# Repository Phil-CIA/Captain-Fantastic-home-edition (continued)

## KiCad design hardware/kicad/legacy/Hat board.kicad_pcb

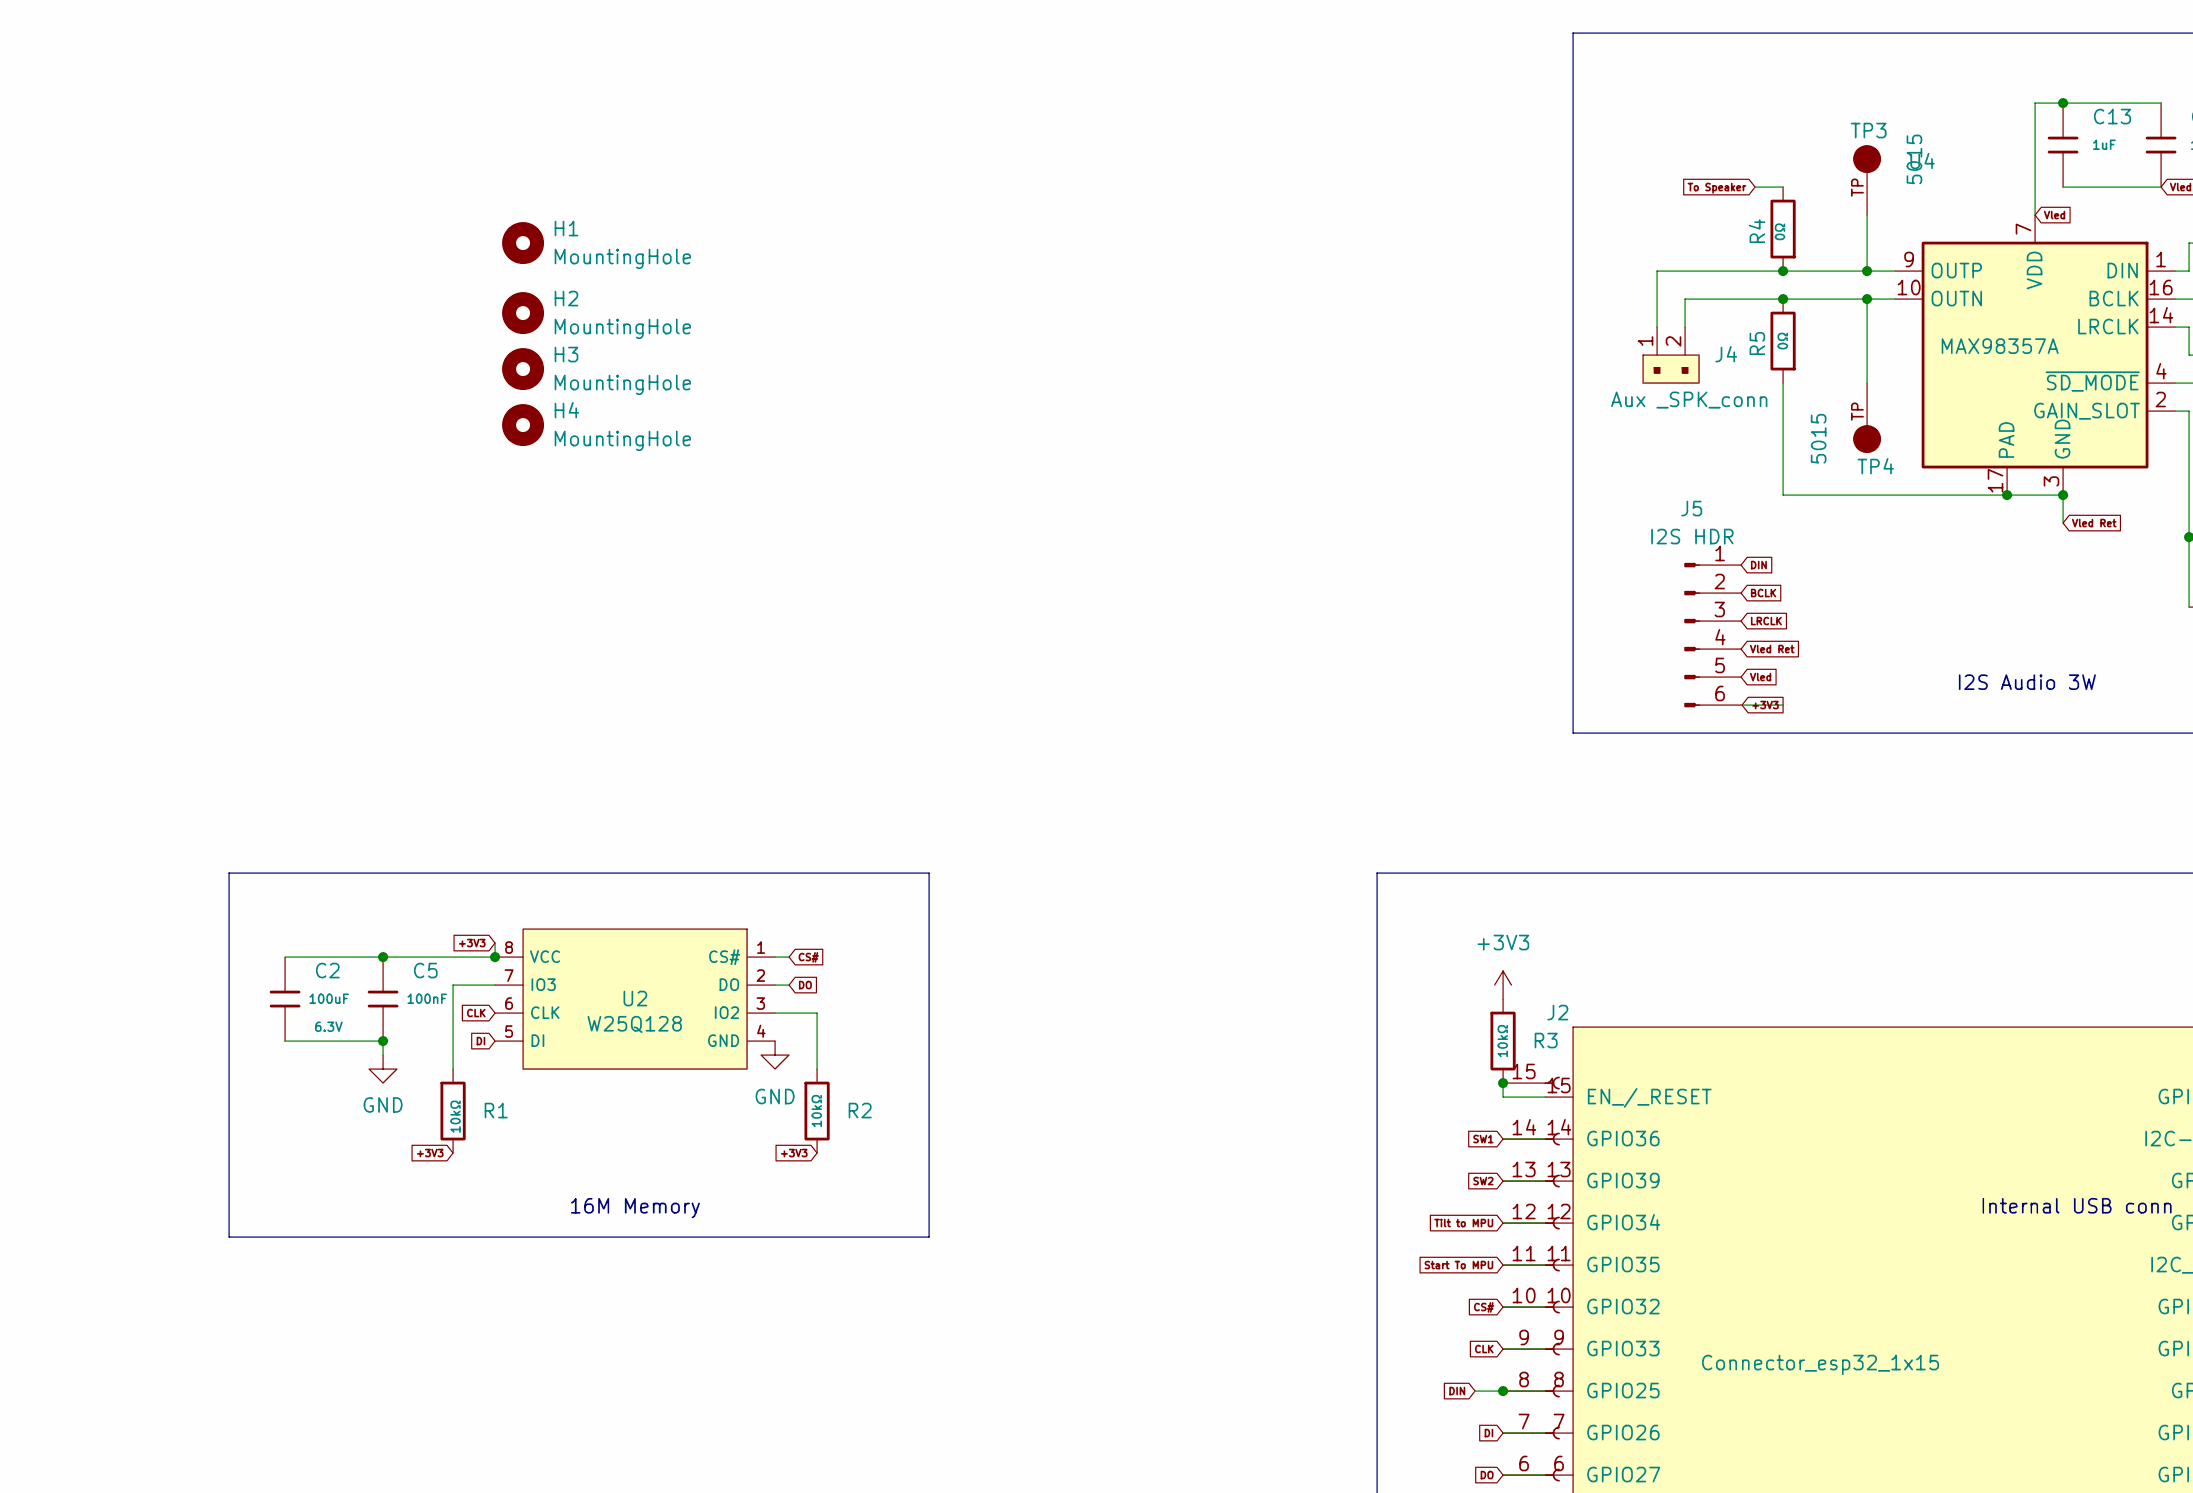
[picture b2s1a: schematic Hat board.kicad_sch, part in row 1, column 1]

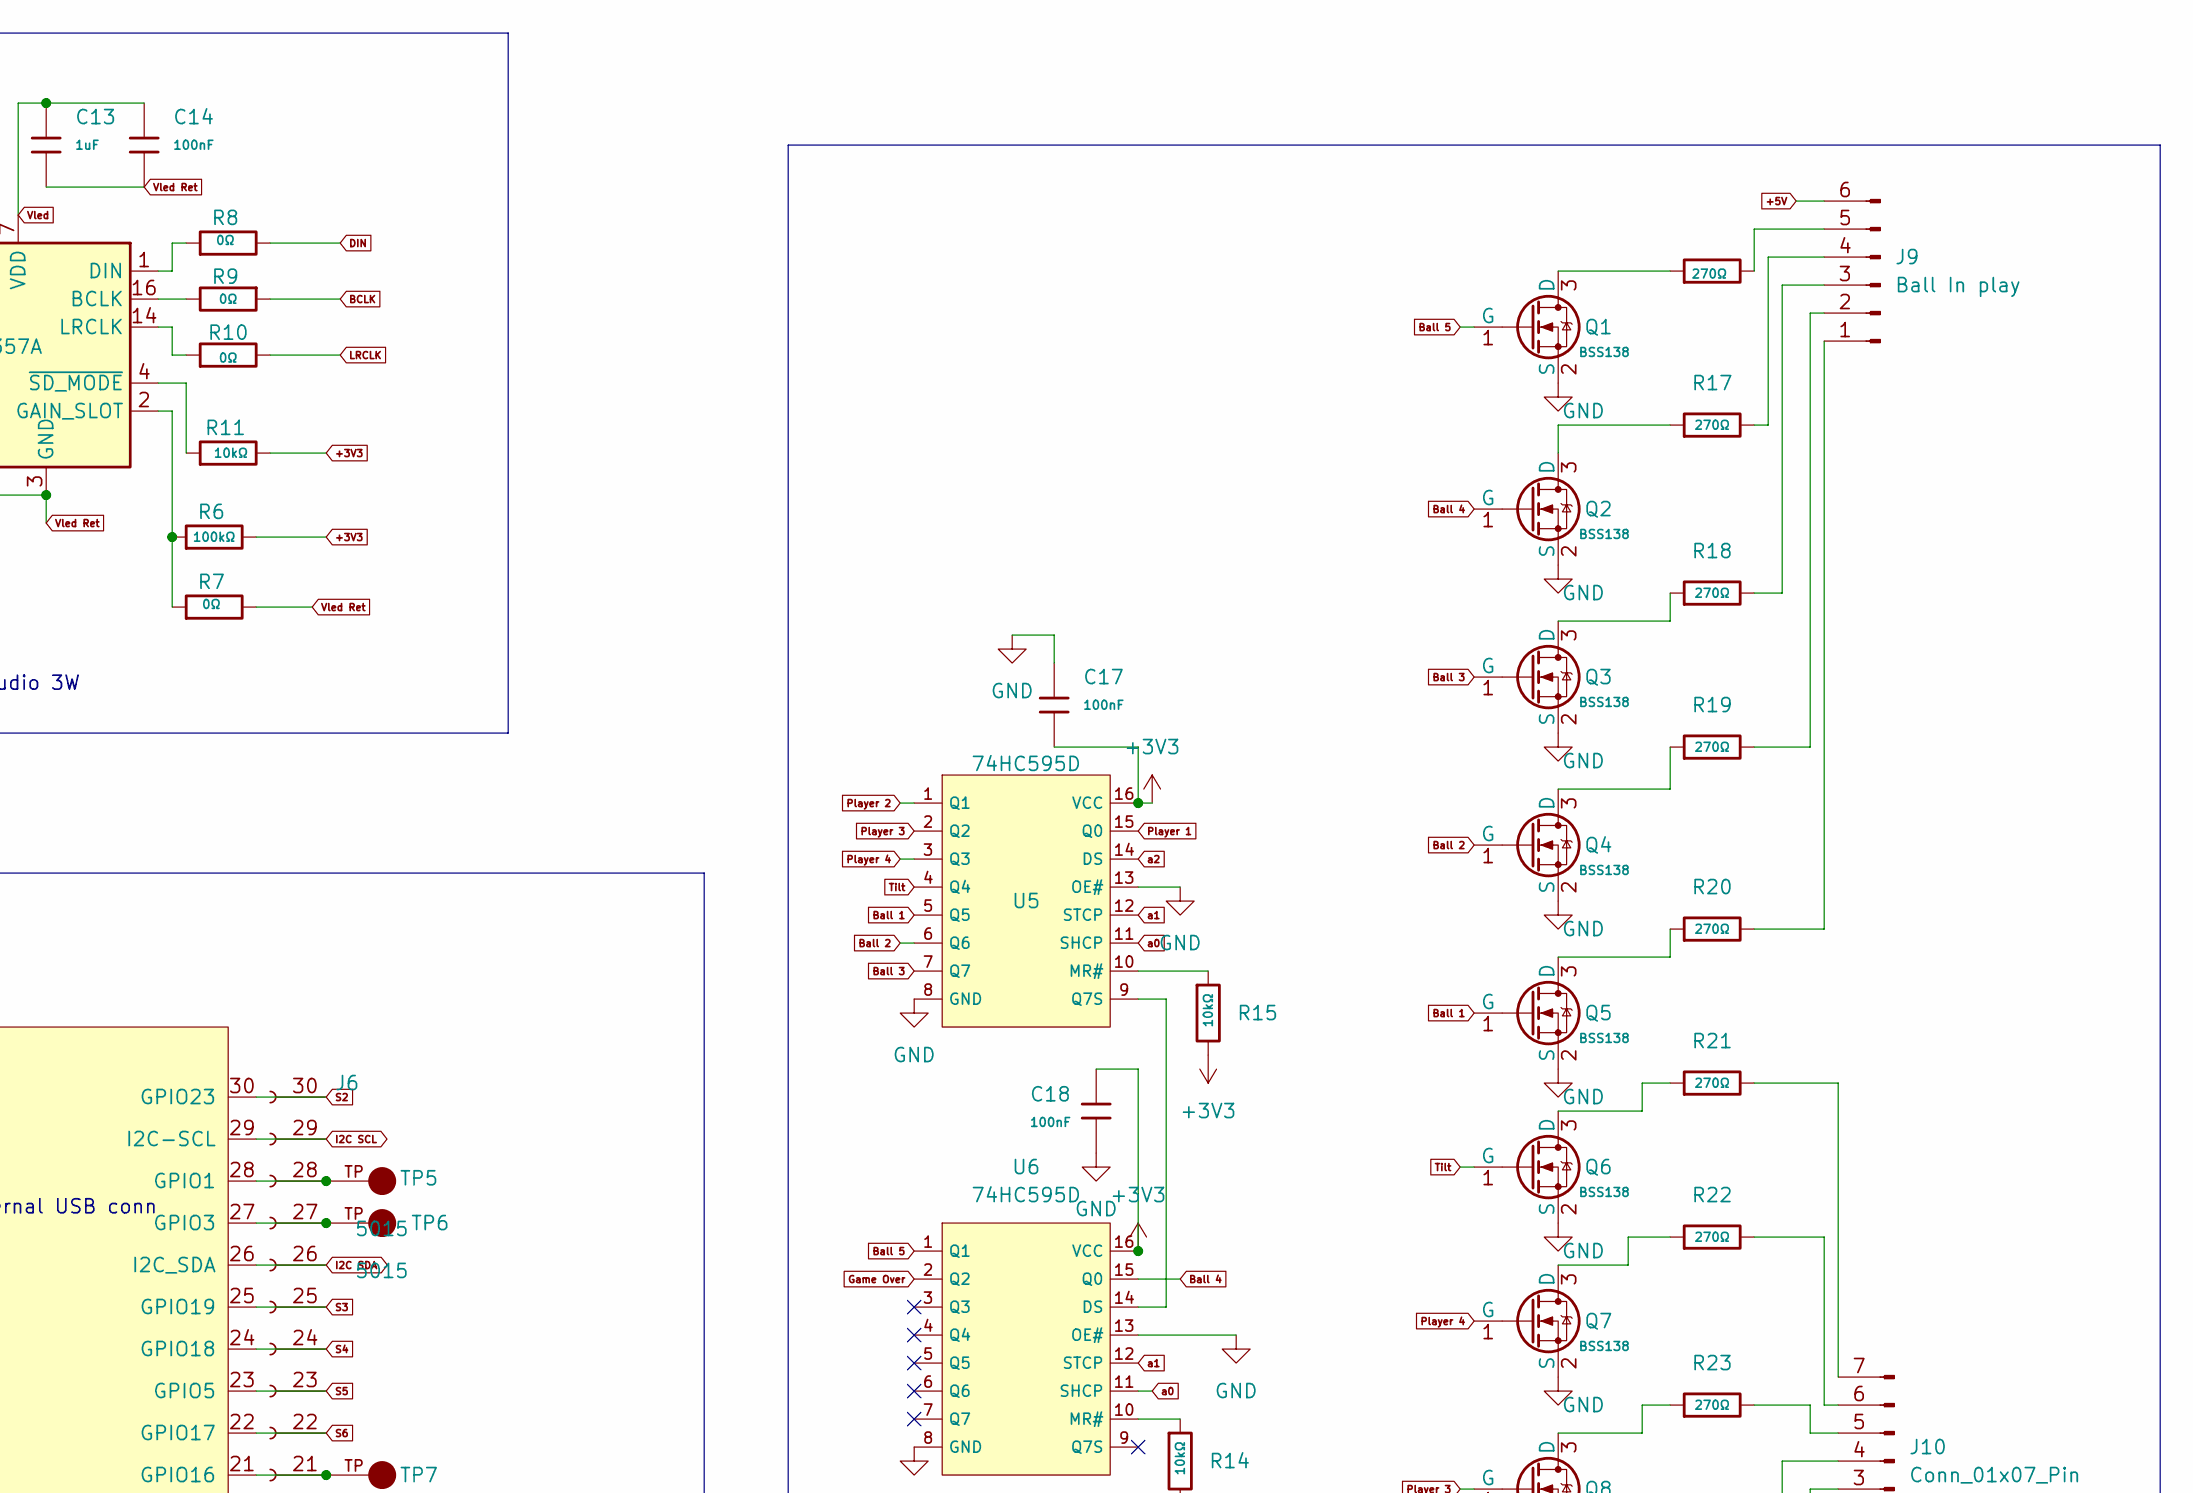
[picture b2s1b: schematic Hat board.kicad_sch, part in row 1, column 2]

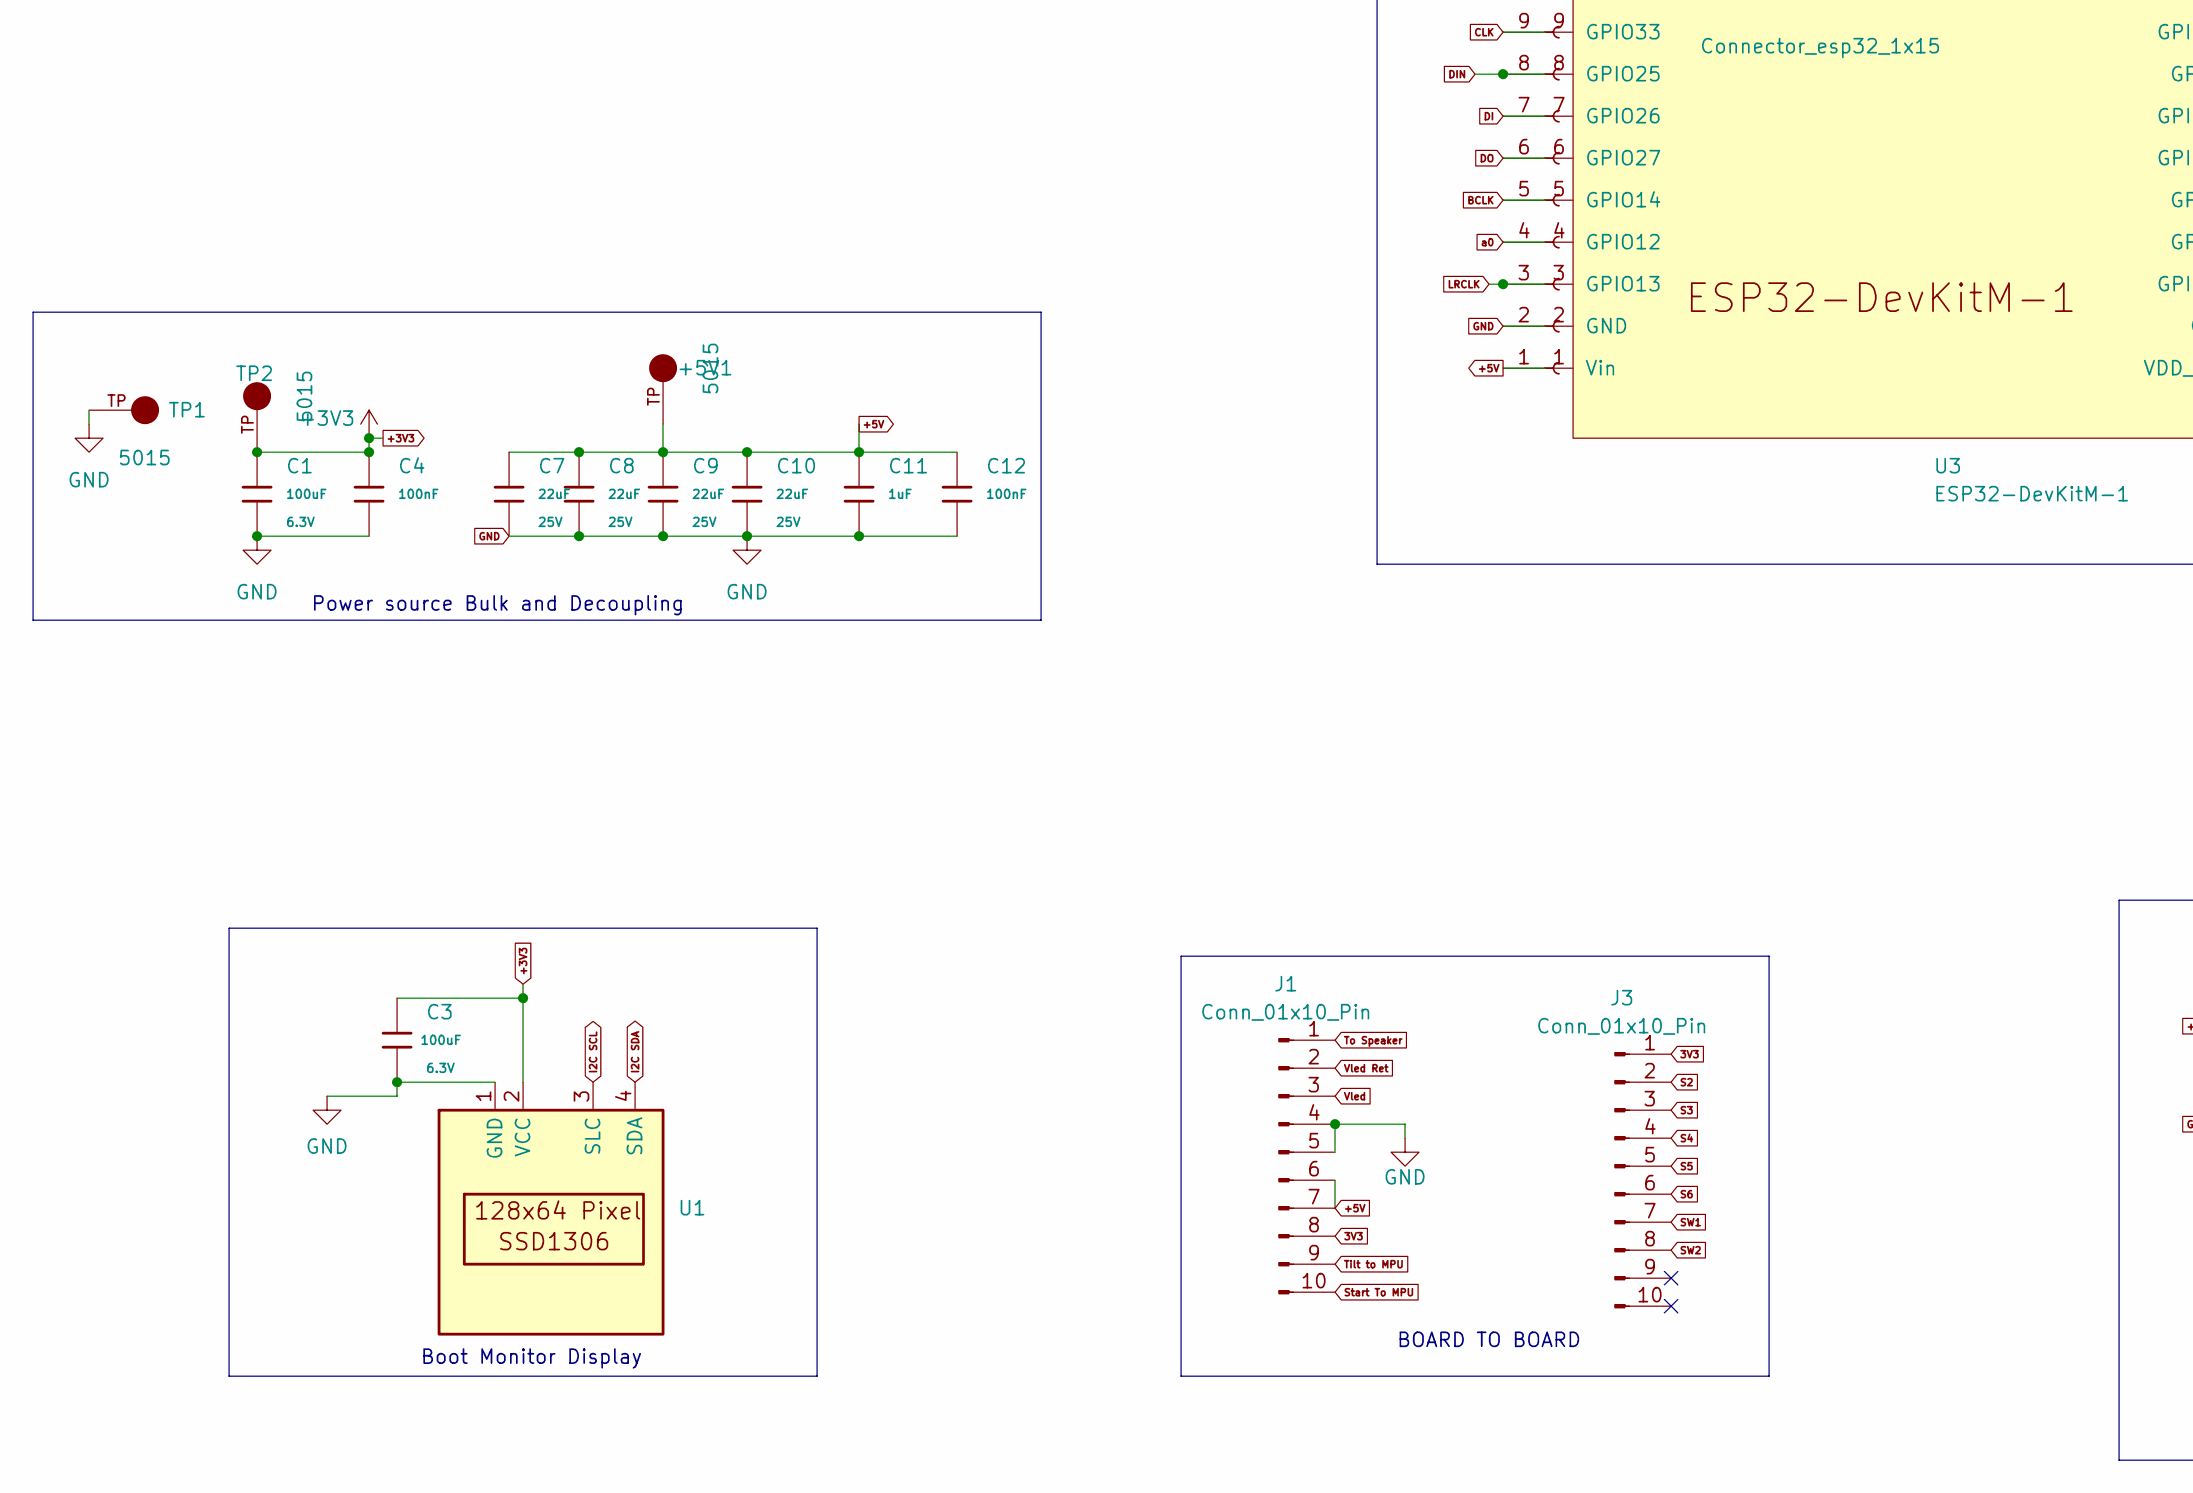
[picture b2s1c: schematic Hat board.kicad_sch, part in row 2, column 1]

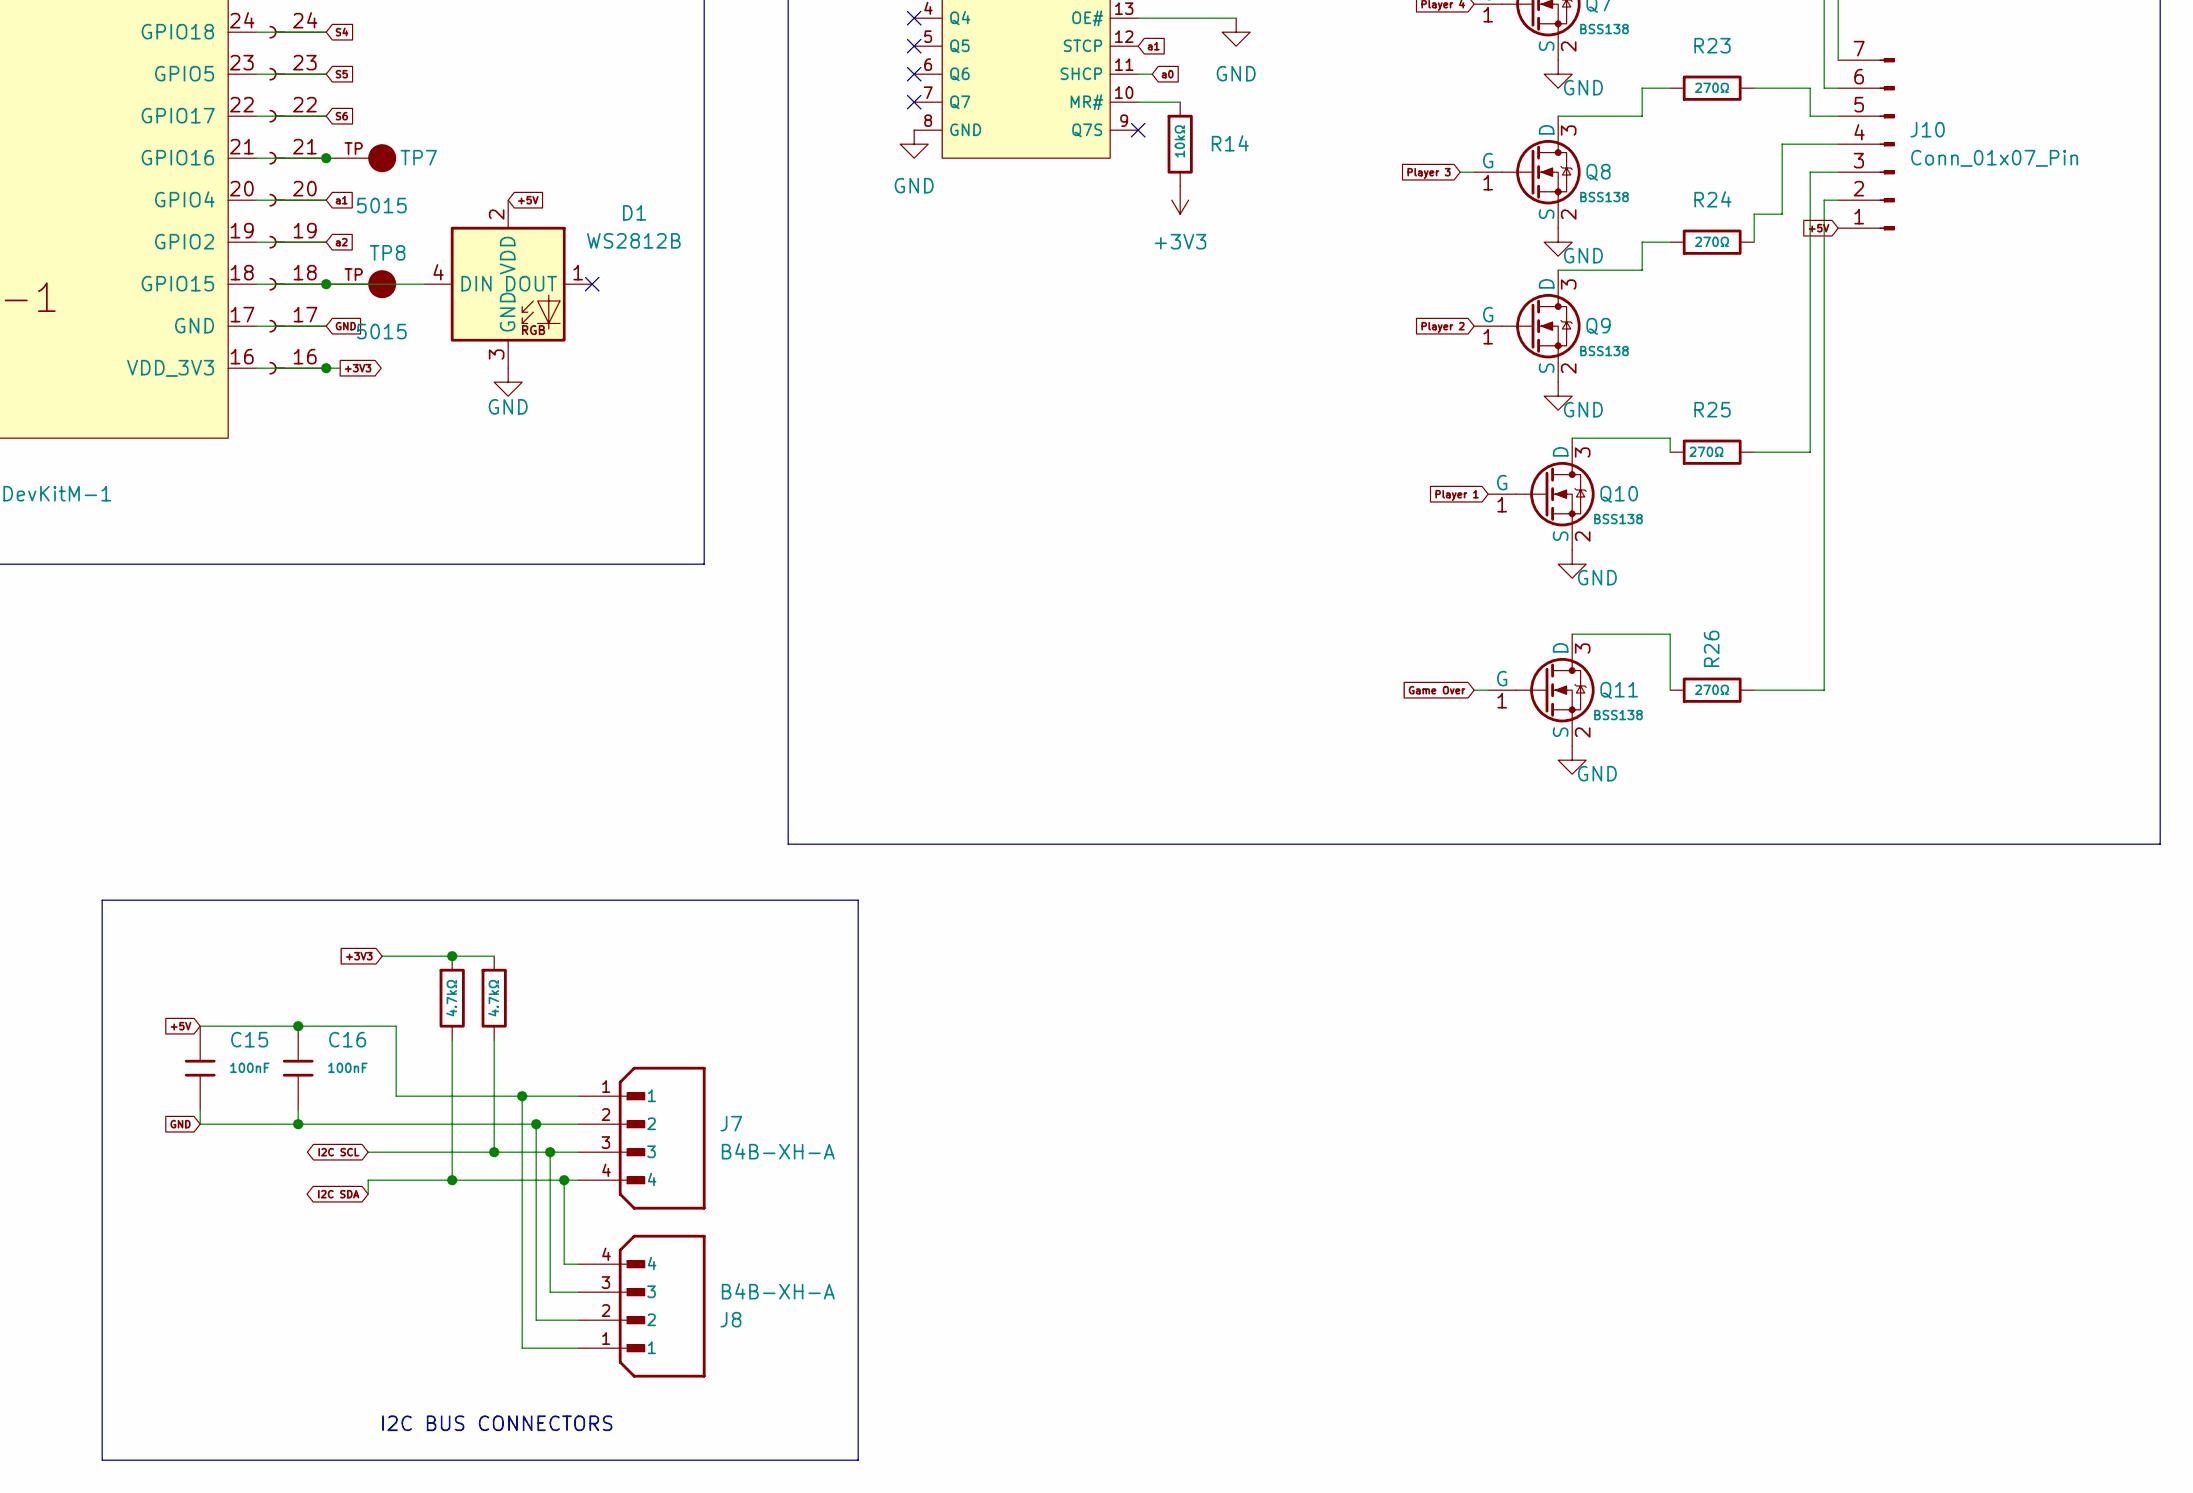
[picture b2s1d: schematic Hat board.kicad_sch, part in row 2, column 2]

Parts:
+5V1: 5015; KEYSTONE_5015; MPN 5015; Digi-Key_PN 36-5015CT-ND
C1, C2, C3: 100uF; C_1206; Voltage Rated 6.3V; Tolerance ±20%; Part CL31A107MQHNNNE; LCSC C15008
C4, C5, C12, C14, C15, C16, C17, C18: 100nF; C_0805; Voltage Rated 50V; Tolerance ±10%; Part CC0805KRX7R9BB104; LCSC C49678
C7, C8, C9, C10: 22uF; C_0805; Voltage Rated 25V; Tolerance ±20%; Part CL21A226MAQNNNE; LCSC C45783
C11, C13: 1uF; C_0805; Voltage Rated 50V; Tolerance ±10%; Part CL21B105KBFNNNE; LCSC C28323
D1: WS2812B; LED-SMD_4P-L1.6-W1.5_XL-1615RGBC-WS2812B; LCSC C5349954
H1, H2, H3, H4: MountingHole; MountingHole_3.5mm_Pad
J1, J3: Conn_01x10_Pin; PinHeader_1x10_P2.54mm_Vertical
J2, J6: Connector_esp32_1x15; PinSocket_1x15_P2.54mm_Vertical
J4: Aux _SPK_conn; JST_XH_B2B-XH-A_1x02_P2.50mm_Vertical; MPN B2B-XH-A(LF)(SN); Digi-Key_PN 455-2247-ND
J5: I2S HDR; PinHeader_1x06_P2.54mm_Vertical_SMD_Pin1Right
J7, J8: B4B-XH-A; JST_EH_B4B-EH-A_1x04_P2.50mm_Vertical; PARTREV 7/4/21
J9: Ball In play; JST_XH_B6B-XH-AM_1x06_P2.50mm_Vertical
J10: Conn_01x07_Pin; JST_XH_B7B-XH-AM_1x07_P2.50mm_Vertical
Q1, Q2, Q3, Q4, Q5, Q6, Q7, Q8, Q9, Q10, Q11: BSS138; Q_SOT-23; Part BSS138; LCSC C7420339
R1, R2, R3, R11, R14, R15: 10kΩ; R_0805; Overload Voltage (Max) 150V; Tolerance ±1%; Part 0805W8F1002T5E; LCSC C17414
R4, R5, R7, R8, R9, R10: 0Ω; R_0805; Overload Voltage (Max) 150V; Tolerance ±1%; Part 0805W8F0000T5E; LCSC C17477
R6: 100kΩ; R_0805; Overload Voltage (Max) 150V; Tolerance ±1%; Part 0805W8F1003T5E; LCSC C149504
R12, R13: 4.7kΩ; R_0805; Overload Voltage (Max) 150V; Tolerance ±1%; Part 0805W8F4701T5E; LCSC C17673
R16, R17, R18, R19, R20, R21, R22, R23, R24, R25, R26: 270Ω; R_0805; Overload Voltage (Max) 150V; Tolerance ±1%; Part 0805W8F2700T5E; LCSC C17590
TP1, TP2, TP3, TP4, TP6, TP7, TP8: 5015; KEYSTONE_5015; MPN 5015; Digi-Key_PN 36-5015CT-ND
TP5: 5015; KEYSTONE_5015; Part 5015; LCSC C5199798
U1: ).96 inOLED display SSD1306
U2: W25Q128; SOIC-8_L5.3-W5.3-P1.27-LS8.0-BL; Part W25Q128JVSIQ; LCSC C97521
U3: ESP32-DevKitM-1
U4: MAX98357A; TQFN-16-1EP_3x3mm_P0.5mm_EP1.23x1.23mm
U5, U6: 74HC595D; SOIC-16_L9.9-W3.9-P1.27-LS6.0-BL; Supply Voltage 2V~6V; Part 74HC595D,118; LCSC C5947

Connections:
3V3: J1.8, J3.1
+3V3: C1.1, C2.1, C3.1, C4.1, C5.1, C17.2, C18.1, J5.6, J6.16 (VDD_3V3), R1.2, R2.2, R3.1, R6.2, R11.2, R12.1, R13.1, R14.2, R15.2, TP2.TP, U1.2 (VCC), U2.8 (VCC), U3.16 (VDD_3V3), U5.16 (VCC), U6.16 (VCC)
+5V: +5V1.TP, C7.1, C8.1, C9.1, C10.1, C11.1, C12.1, C15.1, C16.1, D1.2 (VDD), J1.6, J1.7, J2.1 (Vin), J7.1, J8.1, J9.6, J10.1, U3.1 (Vin)
BCLK: J2.5 (GPIO14), J5.2, R9.1, U3.5 (GPIO14)
Ball 1: Q5.1 (G), U5.5 (Q5)
Ball 2: Q4.1 (G), U5.6 (Q6)
Ball 3: Q3.1 (G), U5.7 (Q7)
Ball 4: Q2.1 (G), U6.15 (Q0)
Ball 5: Q1.1 (G), U6.1 (Q1)
CLK: J2.9 (GPIO33), U2.6 (CLK), U3.9 (GPIO33)
CS#: J2.10 (GPIO32), U2.1 (CS#), U3.10 (GPIO32)
DI: J2.7 (GPIO26), U2.5 (DI), U3.7 (GPIO26)
DIN: J2.8 (GPIO25), J5.1, R8.2, U3.8 (GPIO25)
DO: J2.6 (GPIO27), U2.2 (DO), U3.6 (GPIO27)
GND: C1.2, C2.2, C3.2, C4.2, C5.2, C7.2, C8.2, C9.2, C10.2, C11.2, C12.2, C15.2, C16.2, C17.1, C18.2, D1.3 (GND), H2.1, J1.4, J1.5, J2.2 (GND), J6.17 (GND), J7.2, J8.2, Q1.2 (S), Q2.2 (S), Q3.2 (S), Q4.2 (S), Q5.2 (S), Q6.2 (S), Q7.2 (S), Q8.2 (S), Q9.2 (S), Q10.2 (S), Q11.2 (S), TP1.TP, U1.1 (GND), U2.4 (GND), U3.2 (GND), U3.17 (GND), U5.8 (GND), U5.13 (OE#), U6.8 (GND), U6.13 (OE#)
Game Over: Q11.1 (G), U6.2 (Q2)
I2C SCL: J6.29 (I2C-SCL), J7.3, J8.3, R13.2, U1.3 (SLC), U3.29 (I2C-SCL)
I2C SDA: J6.26 (I2C_SDA), J7.4, J8.4, R12.2, U1.4 (SDA), U3.26 (I2C_SDA)
LRCLK: J2.3 (GPIO13), J5.3, R10.2, U3.3 (GPIO13)
unnamed: D1.4 (DIN), J6.18 (GPIO15), TP8.TP, U3.18 (GPIO15)
unnamed: J2.15 (EN_/_RESET), R3.2, U3.15 (EN_/_RESET)
unnamed: J6.28 (GPIO1), TP5.TP, U3.28 (GPIO1)
unnamed: J6.27 (GPIO3), TP6.TP, U3.27 (GPIO3)
unnamed: J6.21 (GPIO16), TP7.TP, U3.21 (GPIO16)
unnamed: J9.1, R20.2
unnamed: J9.2, R19.2
unnamed: J9.3, R18.2
unnamed: J9.4, R17.2
unnamed: J9.5, R16.2
unnamed: J10.2, R26.2
unnamed: J10.3, R25.2
unnamed: J10.4, R24.2
unnamed: J10.5, R23.2
unnamed: J10.6, R22.2
unnamed: J10.7, R21.2
unnamed: Q1.3 (D), R16.1
unnamed: Q2.3 (D), R17.1
unnamed: Q3.3 (D), R18.1
unnamed: Q4.3 (D), R19.1
unnamed: Q5.3 (D), R20.1
unnamed: Q6.3 (D), R21.1
unnamed: Q7.3 (D), R22.1
unnamed: Q8.3 (D), R23.1
unnamed: Q9.3 (D), R24.1
unnamed: Q10.3 (D), R25.1
unnamed: Q11.3 (D), R26.1
unnamed: R2.1, U2.3 (IO2)
unnamed: R1.1, U2.7 (IO3)
unnamed: R9.2, U4.16 (BCLK)
unnamed: R8.1, U4.1 (DIN)
unnamed: R6.1, R7.1, U4.2 (GAIN_SLOT)
unnamed: R10.1, U4.14 (LRCLK)
unnamed: J4.2, R5.2, TP4.TP, U4.10 (OUTN)
unnamed: J4.1, R4.1, TP3.TP, U4.9 (OUTP)
unnamed: R11.1, U4.4 (~SD_MODE)
unnamed: R15.1, U5.10 (MR#)
unnamed: U5.9 (Q7S), U6.14 (DS)
unnamed: R14.1, U6.10 (MR#)
Player 1: Q10.1 (G), U5.15 (Q0)
Player 2: Q9.1 (G), U5.1 (Q1)
Player 3: Q8.1 (G), U5.2 (Q2)
Player 4: Q7.1 (G), U5.3 (Q3)
S2: J3.2, J6.30 (GPIO23), U3.30 (GPIO23)
S3: J3.3, J6.25 (GPIO19), U3.25 (GPIO19)
S4: J3.4, J6.24 (GPIO18), U3.24 (GPIO18)
S5: J3.5, J6.23 (GPIO5), U3.23 (GPIO5)
S6: J3.6, J6.22 (GPIO17), U3.22 (GPIO17)
SW1: J2.14 (GPIO36), J3.7, U3.14 (GPIO36)
SW2: J2.13 (GPIO39), J3.8, U3.13 (GPIO39)
Start To MPU: J1.10, J2.11 (GPIO35), U3.11 (GPIO35)
Tilt: Q6.1 (G), U5.4 (Q4)
Tilt to MPU: J1.9, J2.12 (GPIO34), U3.12 (GPIO34)
To Speaker: J1.1, R4.2
Vled: C13.1, C14.1, J1.3, J5.5, U4.7 (VDD), U4.8 (VDD)
Vled Ret: C13.2, C14.2, J1.2, J5.4, R5.1, R7.2, U4.3 (GND), U4.11 (GND), U4.15 (GND), U4.17 (PAD)
a0: J2.4 (GPIO12), U3.4 (GPIO12), U5.11 (SHCP), U6.11 (SHCP)
a1: J6.20 (GPIO4), U3.20 (GPIO4), U5.12 (STCP), U6.12 (STCP)
a2: J6.19 (GPIO2), U3.19 (GPIO2), U5.14 (DS)

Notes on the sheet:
BOARD TO BOARD
Power source Bulk and Decoupling
I2C BUS CONNECTORS
Boot Monitor Display
16M Memory
Internal USB conn
I2S Audio 3W

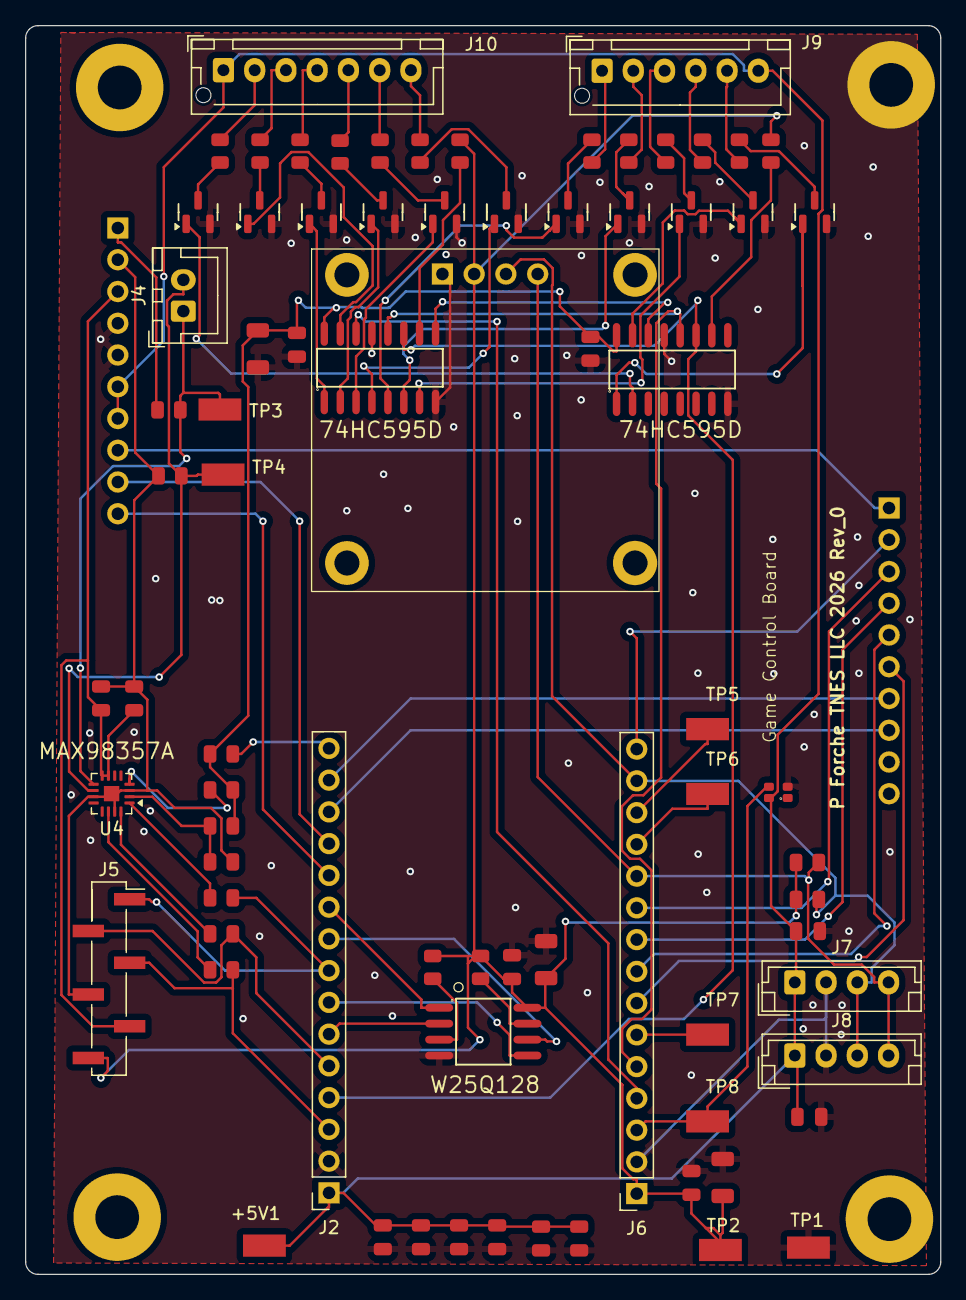
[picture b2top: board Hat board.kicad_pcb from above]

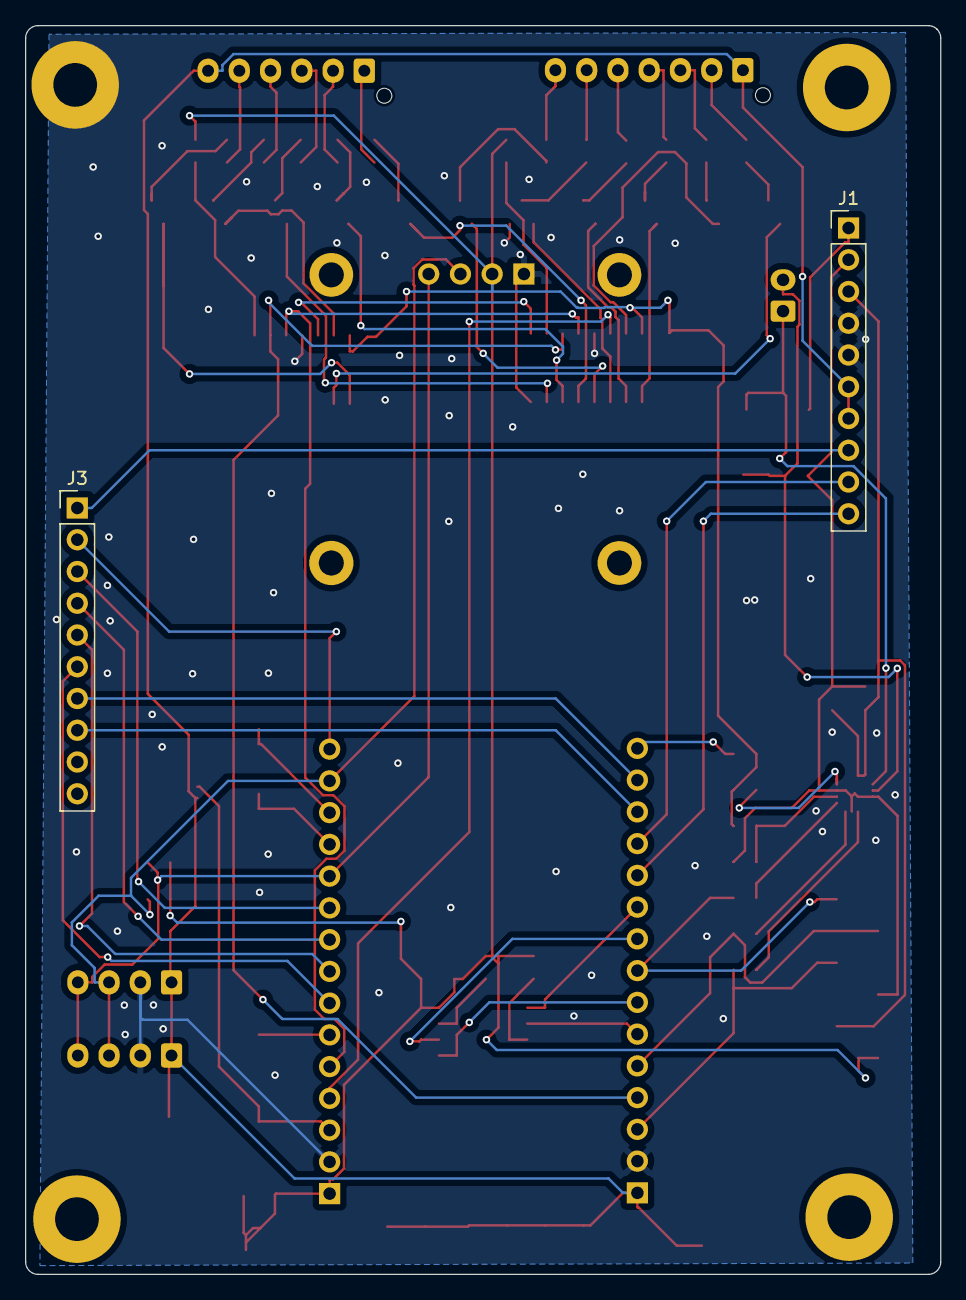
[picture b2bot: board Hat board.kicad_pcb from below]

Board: 2 copper layers, 73.2 x 99.9 mm, 83 parts (2 on the bottom side), 78 nets.

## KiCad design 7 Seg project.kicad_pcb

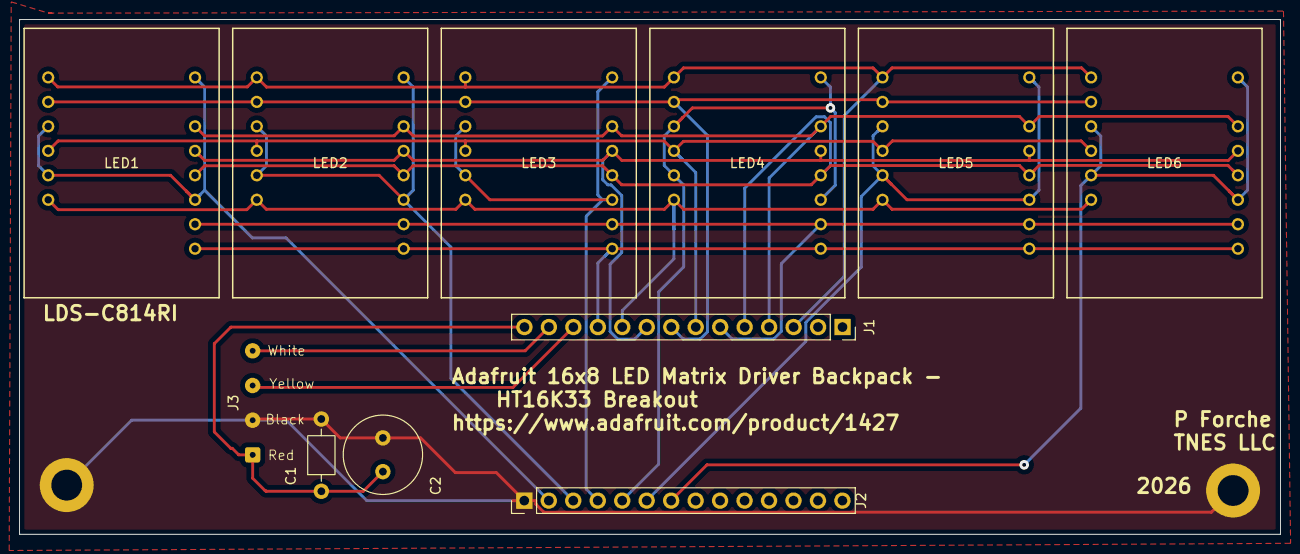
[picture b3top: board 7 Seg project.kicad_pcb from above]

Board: 2 copper layers, 130.9 x 53.4 mm, 13 parts (0 on the bottom side), 19 nets.

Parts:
C1: 0.1 uf; C_Axial_L3.8mm_D2.6mm_P7.50mm_Horizontal
C2: 100uf; C_Radial_D8.0mm_H11.5mm_P3.50mm
J1, J2: Conn_01x14_Socket; PinSocket_1x14_P2.54mm_Vertical
J3: BM04B-SRSS-TB; SolderWire-0.1sqmm_1x04_P3.6mm_D0.4mm_OD1mm
LED1, LED2, LED3, LED4, LED5, LED6: LDS-C814RI; LDS-C814RI_LUM
REF 2: MountingHole_3.2mm_M3_DIN965_Pad
lb: MountingHole_3.2mm_M3_DIN965_Pad

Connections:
A0: J1.9, LED1.13 (G), LED2.13 (G), LED3.13 (G), LED4.13 (G), LED5.13 (G), LED6.13 (G)
A1: J1.10, LED1.6 (LDP), LED2.6 (LDP), LED3.6 (LDP), LED4.6 (LDP), LED5.6 (LDP), LED6.6 (LDP)
A2: J1.11, LED1.9 (RDP), LED2.9 (RDP), LED3.9 (RDP), LED4.9 (RDP), LED5.9 (RDP), LED6.9 (RDP)
ANOD3: J1.8, LED1.2 (F), LED2.2 (F), LED3.2 (F), LED4.2 (F), LED5.2 (F), LED6.2 (F)
ANOD4: J1.7, LED1.4 (E), LED2.4 (E), LED3.4 (E), LED4.4 (E), LED5.4 (E), LED6.4 (E)
ANOD5: J1.6, LED1.10 (D), LED2.10 (D), LED3.10 (D), LED4.10 (D), LED5.10 (D), LED6.10 (D)
ANOD6: J1.5, LED1.12 (C), LED2.12 (C), LED3.12 (C), LED4.12 (C), LED5.12 (C), LED6.12 (C)
ANOD7: J1.4, LED1.14 (B), LED2.14 (B), LED3.14 (B), LED4.14 (B), LED5.14 (B), LED6.14 (B)
ANOD8: J1.3, LED1.1 (A), LED2.1 (A), LED3.1 (A), LED4.1 (A), LED5.1 (A), LED6.1 (A)
CATH0: J2.2, LED1.3 (com), LED1.5 (COM), LED1.11 (COM), LED1.16 (COM)
CATH1: J2.3, LED2.3 (com), LED2.5 (COM), LED2.11 (COM), LED2.16 (COM)
CATH2: J2.4, LED3.3 (com), LED3.5 (COM), LED3.11 (COM), LED3.16 (COM)
CATH3: J2.5, LED4.3 (com), LED4.5 (COM), LED4.11 (COM), LED4.16 (COM)
CATH4: J2.6, LED5.3 (com), LED5.5 (COM), LED5.11 (COM), LED5.16 (COM)
CATH5: J2.7, LED6.3 (com), LED6.5 (COM), LED6.11 (COM), LED6.16 (COM)
GND: C1.2, C2.2, J2.1, J3.2, REF 2.1, lb.1
SDA: J1.13, J3.4
SLC: J1.12, J3.3
VDD: C1.1, C2.1, J1.14, J3.1
